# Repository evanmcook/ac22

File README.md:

# ac22
an 8 key macropad

* pcb from [OSHPark](https://oshpark.com)
* acrylic from [ponoko](https://ponoko.com)
* microcontrollers and keyswitches from [boardsource.xyz](https://boardsource.xyz)
* keycaps from [signature plastics](https://pimpmykeyboard.com) in BFV, RCG, WAN for blue, pink, white
* m2 hardware from a kit
* firmware from [QMK](https://qmk.fm/)

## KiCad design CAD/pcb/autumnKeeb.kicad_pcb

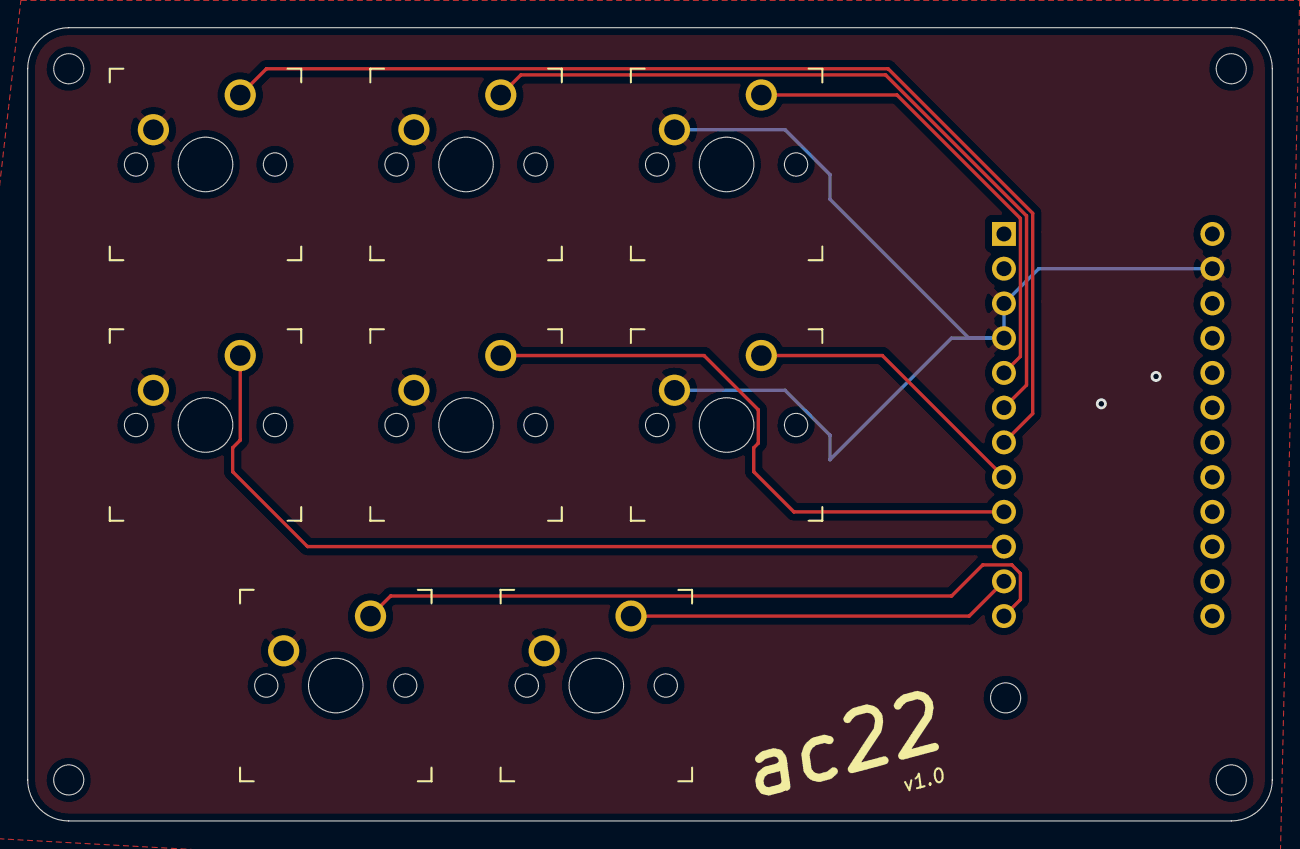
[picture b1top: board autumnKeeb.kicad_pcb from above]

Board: 2 copper layers, 91.0 x 58.0 mm, 10 parts (0 on the bottom side), 9 nets.

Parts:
SW1, SW2, SW3, SW4, SW5, SW6, SW7, SW8: SW_Push; SW_MX
U1: ProMicro; ArduinoProMicro
e: MountingHole_2.2mm_M2

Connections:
GND: SW1.2, SW2.2, SW3.2, SW4.2, SW5.2, SW6.2, SW7.2, SW8.2, U1.3, U1.4, U1.23
row1: SW1.1, U1.5
row2: SW2.1, U1.6
row3: SW3.1, U1.7
row4: SW4.1, U1.8
row5: SW5.1, U1.9
row6: SW6.1, U1.10
row7: SW7.1, U1.11
row8: SW8.1, U1.12

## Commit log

2021-02-02 Update README.md
    added details
2021-02-19 Update README.md
    spelling
2021-02-19 resources v1
    added cad, firmware, images
